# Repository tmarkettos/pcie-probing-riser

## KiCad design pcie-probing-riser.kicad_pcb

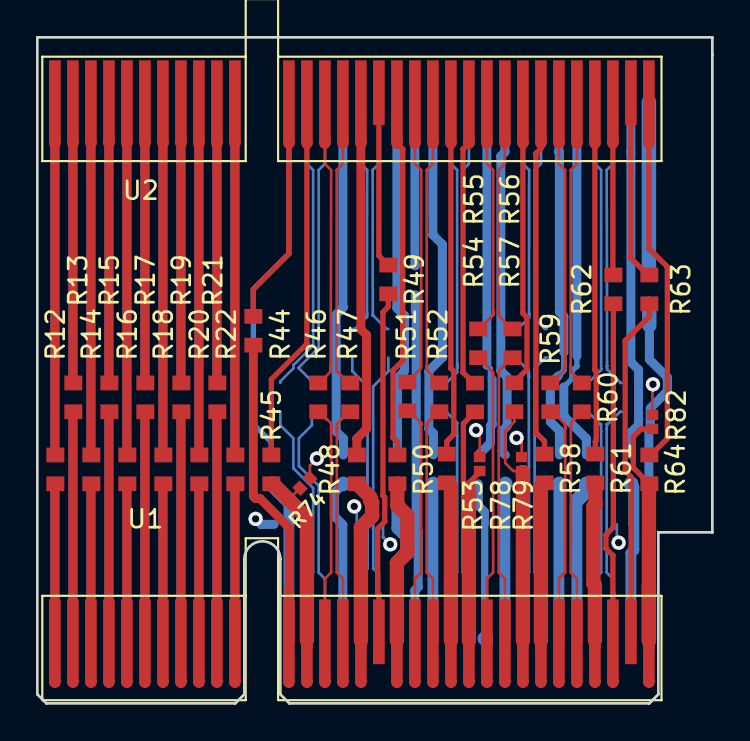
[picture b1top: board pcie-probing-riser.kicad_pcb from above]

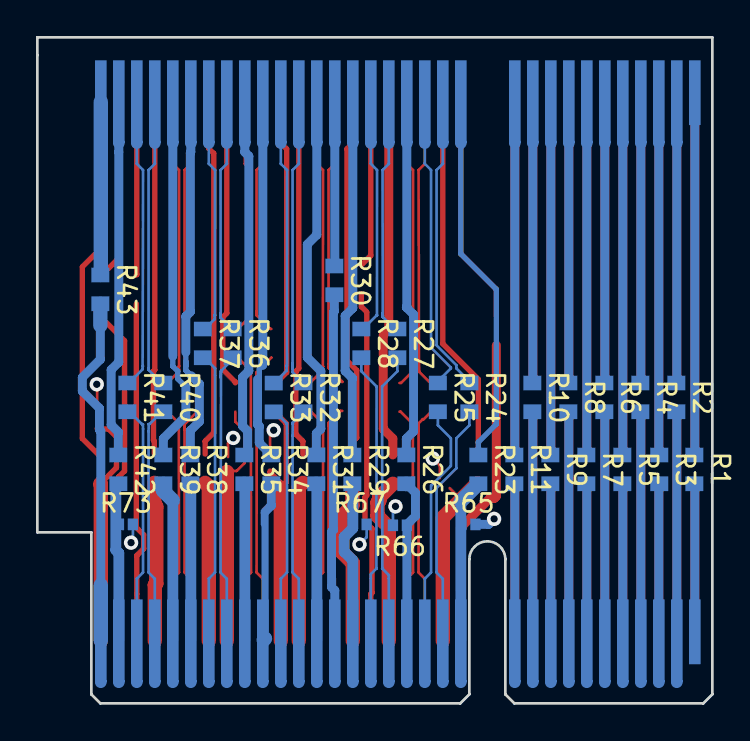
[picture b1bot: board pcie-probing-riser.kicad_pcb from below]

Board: 4 copper layers, 37.5 x 37.0 mm, 74 parts (36 on the bottom side), 130 nets.

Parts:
R1, R2, R3, R4, R5, R6, R7, R8, R9, R10, R11, R12, R13, R14, R15, R16, R17, R18, R19, R20, R21, R22, R23, R24, R25, R26, R27, R28, R29, R30, R31, R32, R33, R34, R35, R36, R37, R38, R39, R40, R41, R42, R43, R44, R45, R46, R47, R48, R49, R50, R51, R52, R53, R54, R55, R56, R57, R58, R59, R60, R61, R62, R63, R64: 0R; R_0603_1608Metric
R65, R66, R67, R73, R74, R78, R79, R82: 0R; R_0402_1005Metric
U1, U2: PCIexpress_x4; BUS_PCIexpress_x4

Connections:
/PCIe_Power/A1: R1.1, U2.A1
/PCIe_Power/A2: R2.1, U2.A2
/PCIe_Power/A3: R3.1, U2.A3
/PCIe_Power/A4: R4.1, U2.A4
/PCIe_Power/A5: R5.1, U2.A5
/PCIe_Power/A6: R6.1, U2.A6
/PCIe_Power/A7: R7.1, U2.A7
/PCIe_Power/A8: R8.1, U2.A8
/PCIe_Power/A9: R9.1, U2.A9
/PCIe_Power/A10: R10.1, U2.A10
/PCIe_Power/A11: R11.1, U2.A11
/PCIe_Power/B1: R12.1, U2.B1
/PCIe_Power/B2: R13.1, U2.B2
/PCIe_Power/B3: R14.1, U2.B3
/PCIe_Power/B4: R15.1, U2.B4
/PCIe_Power/B5: R16.1, U2.B5
/PCIe_Power/B6: R17.1, U2.B6
/PCIe_Power/B7: R18.1, U2.B7
/PCIe_Power/B8: R19.1, U2.B8
/PCIe_Power/B9: R20.1, U2.B9
/PCIe_Power/B10: R21.1, U2.B10
/PCIe_Power/B11: R22.1, U2.B11
/PCIe_Power/GNDA4: R4.2, U1.A4
/PCIe_Power/GNDB4: R15.2, U1.B4
/PCIe_Power/GNDB7: R18.2, U1.B7
/PCIe_data/A12: R23.1, U2.A12
/PCIe_data/A15: R26.1, U2.A15
/PCIe_data/A18: R29.1, U2.A18
/PCIe_data/A19: R30.1, U2.A19
/PCIe_data/A20: R31.1, U2.A20
/PCIe_data/A23: R34.1, U2.A23
/PCIe_data/A24: R35.1, U2.A24
/PCIe_data/A27: R38.1, U2.A27
/PCIe_data/A28: R39.1, U2.A28
/PCIe_data/A31: R42.1, U2.A31
/PCIe_data/A32: R43.1, U2.A32
/PCIe_data/B12: R44.1, U2.B12
/PCIe_data/B13: R45.1, U2.B13
/PCIe_data/B16: R48.1, U2.B16
/PCIe_data/B17: R49.1, U2.B17
/PCIe_data/B18: R50.1, U2.B18
/PCIe_data/B21: R53.1, U2.B21
/PCIe_data/B22: R54.1, U2.B22
/PCIe_data/B25: R57.1, U2.B25
/PCIe_data/B26: R58.1, U2.B26
/PCIe_data/B29: R61.1, U2.B29
/PCIe_data/B30: R62.1, U2.B30
/PCIe_data/B31: R63.1, U2.B31
/PCIe_data/B32: R64.1, U2.B32
/PCIe_data/GNDA: R65.2, R66.2, R67.2, R73.2
/PCIe_data/GNDA12: R23.2, R65.1, U1.A12
/PCIe_data/GNDA15: R26.2, R66.1, U1.A15
/PCIe_data/GNDA18: R29.2, R67.1, U1.A18
/PCIe_data/GNDA20: R31.2, U1.A20
/PCIe_data/GNDA23: R34.2, U1.A23
/PCIe_data/GNDA24: R35.2, U1.A24
/PCIe_data/GNDA27: R38.2, U1.A27
/PCIe_data/GNDA28: R39.2, U1.A28
/PCIe_data/GNDA31: R42.2, R73.1, U1.A31
/PCIe_data/GNDA32: R43.2, U1.A32
/PCIe_data/GNDB: R74.2, R78.2, R79.2, R82.2
/PCIe_data/GNDB13: R45.2, R74.1, U1.B13
/PCIe_data/GNDB16: R48.2, U1.B16
/PCIe_data/GNDB18: R50.2, U1.B18
/PCIe_data/GNDB21: R53.2, U1.B21
/PCIe_data/GNDB22: R54.2, R78.1, U1.B22
/PCIe_data/GNDB25: R57.2, R79.1, U1.B25
/PCIe_data/GNDB26: R58.2, U1.B26
/PCIe_data/GNDB29: R61.2, U1.B29
/PCIe_data/GNDB32: R64.2, R82.1, U1.B32
/PCIe_data/I0_N: R28.2, U1.A17
/PCIe_data/I0_P: R27.2, U1.A16
/PCIe_data/I1_N: R33.2, U1.A22
/PCIe_data/I1_P: R32.2, U1.A21
/PCIe_data/I2_N: R37.2, U1.A26
/PCIe_data/I2_P: R36.2, U1.A25
/PCIe_data/I3_N: R41.2, U1.A30
/PCIe_data/I3_P: R40.2, U1.A29
/PCIe_data/O0_N: R47.2, U1.B15
/PCIe_data/O0_P: R46.2, U1.B14
/PCIe_data/O1_N: R52.2, U1.B20
/PCIe_data/O1_P: R51.2, U1.B19
/PCIe_data/O2_N: R56.2, U1.B24
/PCIe_data/O2_P: R55.2, U1.B23
/PCIe_data/O3_N: R60.2, U1.B28
/PCIe_data/O3_P: R59.2, U1.B27
/PCIe_data/R0_N: R28.1, U2.A17
/PCIe_data/R0_P: R27.1, U2.A16
/PCIe_data/R1_N: R33.1, U2.A22
/PCIe_data/R1_P: R32.1, U2.A21
/PCIe_data/R2_N: R37.1, U2.A26
/PCIe_data/R2_P: R36.1, U2.A25
/PCIe_data/R3_N: R41.1, U2.A30
/PCIe_data/R3_P: R40.1, U2.A29
/PCIe_data/REFCLK_N: R25.2, U1.A14
/PCIe_data/REFCLK_P: R24.2, U1.A13
/PCIe_data/REFCLKo_N: R25.1, U2.A14
/PCIe_data/REFCLKo_P: R24.1, U2.A13
/PCIe_data/T0_N: R47.1, U2.B15
/PCIe_data/T0_P: R46.1, U2.B14
/PCIe_data/T1_N: R52.1, U2.B20
/PCIe_data/T1_P: R51.1, U2.B19
/PCIe_data/T2_N: R56.1, U2.B24
/PCIe_data/T2_P: R55.1, U2.B23
/PCIe_data/T3_N: R60.1, U2.B28
/PCIe_data/T3_P: R59.1, U2.B27
unnamed: R1.2, U1.A1
unnamed: R2.2, U1.A2
unnamed: R3.2, U1.A3
unnamed: R5.2, U1.A5
unnamed: R6.2, U1.A6
unnamed: R7.2, U1.A7
unnamed: R8.2, U1.A8
unnamed: R9.2, U1.A9
unnamed: R10.2, U1.A10
unnamed: R11.2, U1.A11
unnamed: R12.2, U1.B1
unnamed: R13.2, U1.B2
unnamed: R14.2, U1.B3
unnamed: R16.2, U1.B5
unnamed: R17.2, U1.B6
unnamed: R19.2, U1.B8
unnamed: R20.2, U1.B9
unnamed: R21.2, U1.B10
unnamed: R22.2, U1.B11
unnamed: R30.2, U1.A19
unnamed: R44.2, U1.B12
unnamed: R49.2, U1.B17
unnamed: R62.2, U1.B30
unnamed: R63.2, U1.B31

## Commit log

2018-05-16 Import basic PCB, some design rule failures
2018-05-16 Fix DRCs
2018-05-16 Add resistors to ground and ground pour
2018-05-17 Switch x8 connector for x4. Add pours and edge cuts
2018-05-18 Sort out silkscreen labels to sane placement
2018-05-18 Move R74 label to be adjacent
2018-06-15 Add some dimension lines
2018-06-15 Add fabrication outputs (it works!)
2018-06-15 Add a picture of the finished article
2018-06-15 Add footprint for PCIe edge connector, generated by a Python script. The Python is standalone, rather than using hte Kicad Python API.
2018-07-20 Add a script to generate PCI Express through-hole connectors (untested)
2018-07-20 Draw PCIe TH connector courtyard, including lip on B side
